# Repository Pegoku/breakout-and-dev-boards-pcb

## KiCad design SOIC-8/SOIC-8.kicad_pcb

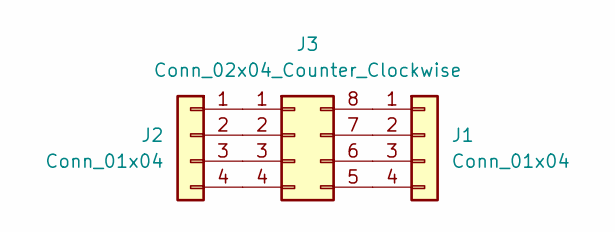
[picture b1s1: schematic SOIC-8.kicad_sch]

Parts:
J1, J2: Conn_01x04; PinHeader_1x04_P2.54mm_Vertical
J3: Conn_02x04_Counter_Clockwise; SOIC-8-1EP_3.9x4.9mm_P1.27mm_EP2.62x3.51mm

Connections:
unnamed: J1.1, J3.8
unnamed: J1.2, J3.7
unnamed: J1.3, J3.6
unnamed: J1.4, J3.5
unnamed: J2.1, J3.1
unnamed: J2.2, J3.2
unnamed: J2.3, J3.3
unnamed: J2.4, J3.4

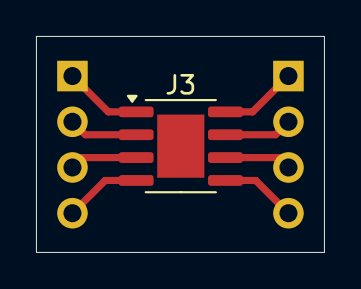
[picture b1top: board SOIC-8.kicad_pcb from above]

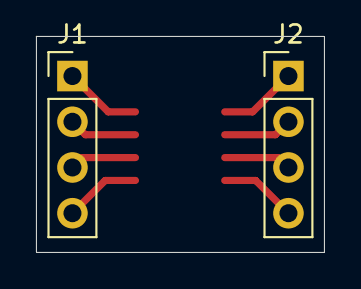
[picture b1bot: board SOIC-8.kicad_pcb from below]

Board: 2 copper layers, 16.0 x 12.0 mm, 3 parts (2 on the bottom side), 8 nets.

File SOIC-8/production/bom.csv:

Designator,Footprint,Quantity,Value,LCSC Part #
"J1, J2",PinHeader_1x04_P2.54mm_Vertical,2,Conn_01x04,
J3,SOIC-8-1EP_3.9x4.9mm_P1.27mm_EP2.62x3.51mm,1,Conn_02x04_Counter_Clockwise,

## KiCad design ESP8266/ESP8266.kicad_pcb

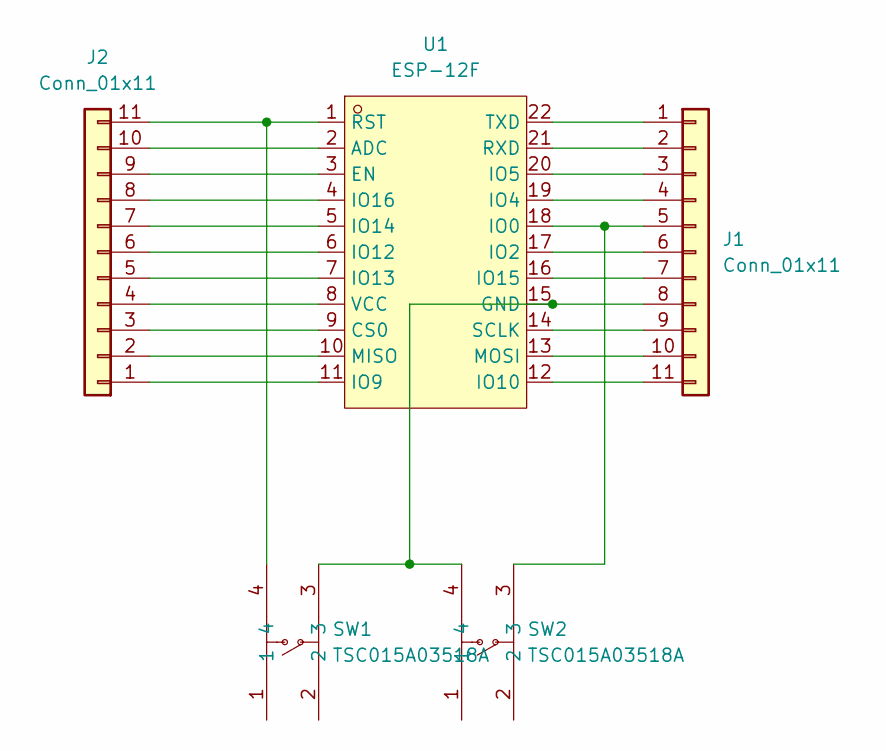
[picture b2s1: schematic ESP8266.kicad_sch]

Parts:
J1, J2: Conn_01x11; PinHeader_1x11_P2.54mm_Vertical
SW1, SW2: TSC015A03518A; KEY-SMD_4P-L4.5-W4.5-P3.00-LS6.8; LCSC Part C2888502
U1: ESP-12F; WIRELM-SMD_ESP-12F; LCSC Part C19949064

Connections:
unnamed: J1.1, U1.22 (TXD)
unnamed: J1.2, U1.21 (RXD)
unnamed: J1.3, U1.20 (IO5)
unnamed: J1.4, U1.19 (IO4)
unnamed: J1.5, SW2.3, U1.18 (IO0)
unnamed: J1.6, U1.17 (IO2)
unnamed: J1.7, U1.16 (IO15)
unnamed: J1.8, SW1.3, SW2.4, U1.15 (GND)
unnamed: J1.9, U1.14 (SCLK)
unnamed: J1.10, U1.13 (MOSI)
unnamed: J1.11, U1.12 (IO10)
unnamed: J2.1, U1.11 (IO9)
unnamed: J2.2, U1.10 (MISO)
unnamed: J2.3, U1.9 (CS0)
unnamed: J2.4, U1.8 (VCC)
unnamed: J2.5, U1.7 (IO13)
unnamed: J2.6, U1.6 (IO12)
unnamed: J2.7, U1.5 (IO14)
unnamed: J2.8, U1.4 (IO16)
unnamed: J2.9, U1.3 (EN)
unnamed: J2.10, U1.2 (ADC)
unnamed: J2.11, SW1.4, U1.1 (RST)

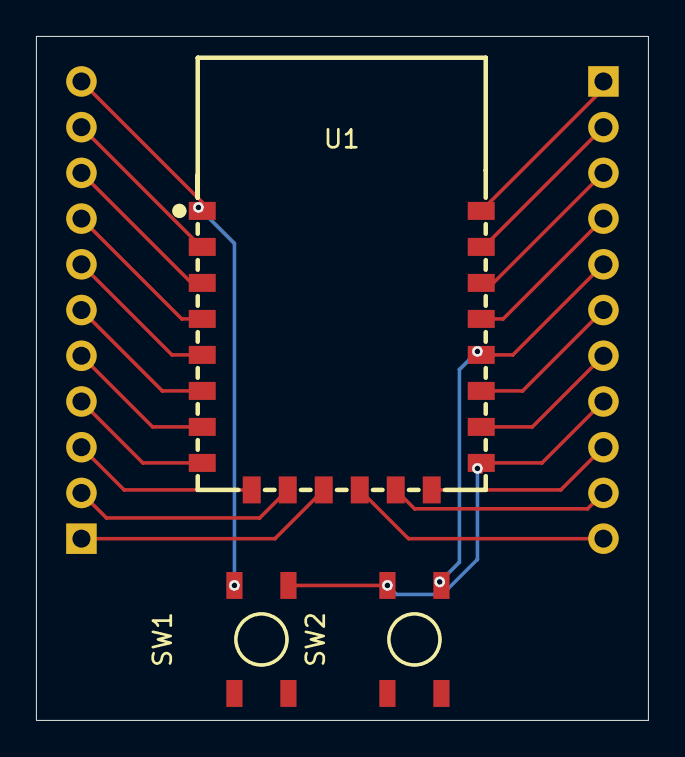
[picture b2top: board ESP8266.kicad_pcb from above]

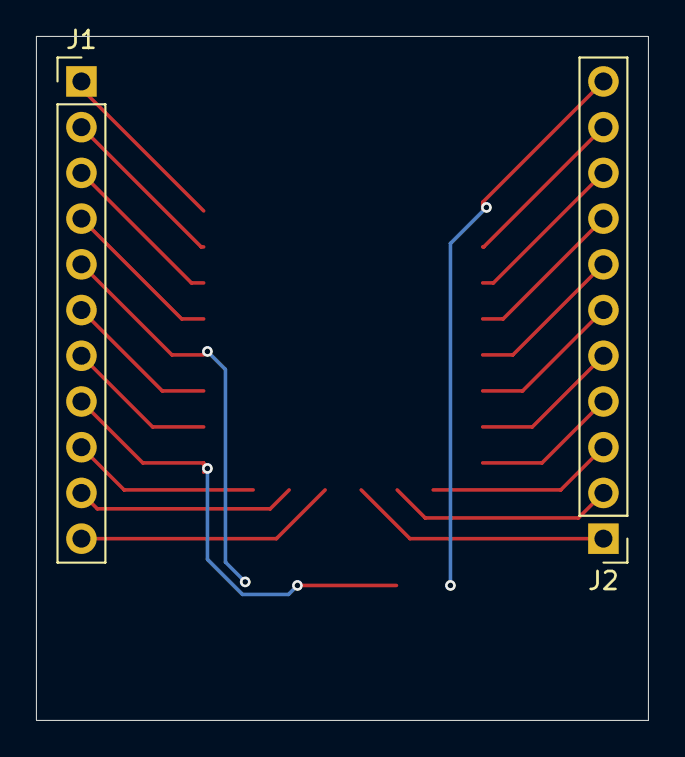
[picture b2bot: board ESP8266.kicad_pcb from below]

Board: 2 copper layers, 34.0 x 38.0 mm, 5 parts (2 on the bottom side), 22 nets.

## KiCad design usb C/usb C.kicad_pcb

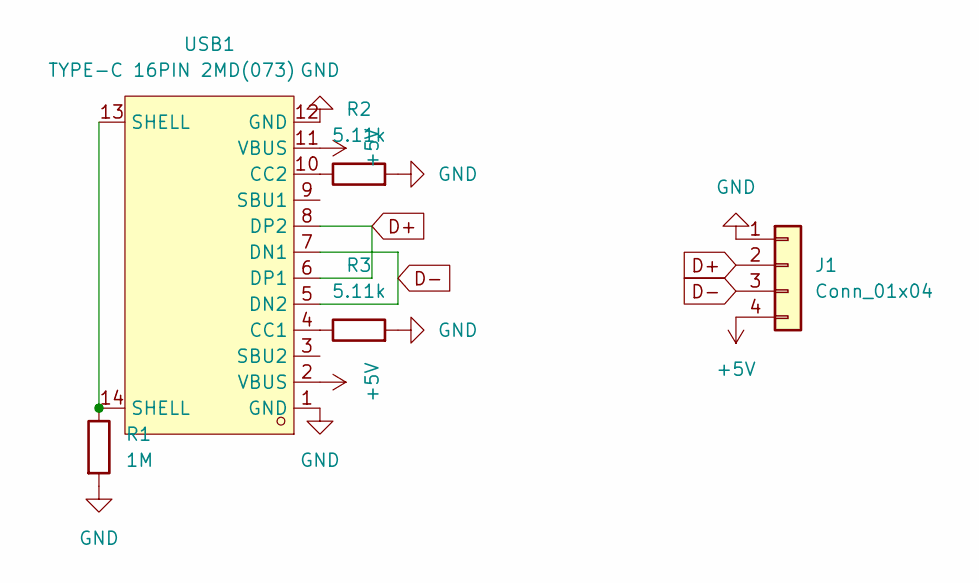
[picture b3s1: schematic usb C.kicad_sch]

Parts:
J1: Conn_01x04; PinHeader_1x04_P2.54mm_Horizontal
R1: 1M; R_0805_2012Metric
R2, R3: 5.11k; R_0805_2012Metric
USB1: TYPE-C 16PIN 2MD(073); USB-C-SMD_TYPE-C-6PIN-2MD-073; LCSC Part C2765186

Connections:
+5V: J1.4, USB1.2 (VBUS), USB1.11 (VBUS)
D+: J1.2, USB1.6 (DP1), USB1.8 (DP2)
D-: J1.3, USB1.5 (DN2), USB1.7 (DN1)
GND: J1.1, R1.2, R2.2, R3.2, USB1.1 (GND), USB1.12 (GND)
unnamed: R1.1, USB1.13 (SHELL), USB1.14 (SHELL)
unnamed: R3.1, USB1.4 (CC1)
unnamed: R2.1, USB1.10 (CC2)

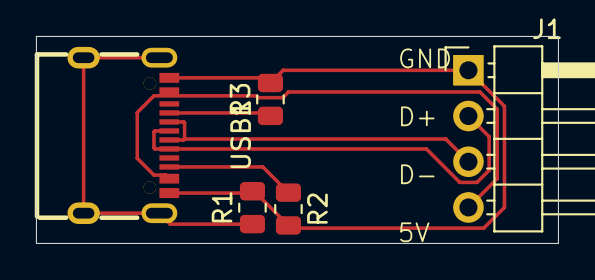
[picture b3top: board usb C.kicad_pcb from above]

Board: 2 copper layers, 29.0 x 11.5 mm, 5 parts (0 on the bottom side), 7 nets.

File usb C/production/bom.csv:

Designator,Footprint,Quantity,Value,LCSC Part #
J1,PinHeader_1x04_P2.54mm_Horizontal,1,Conn_01x04,
R1,0805,1,1M,
"R2, R3",0805,2,5.11k,
USB1,USB-C-SMD_TYPE-C-6PIN-2MD-073,1,TYPE-C 16PIN 2MD(073),C2765186

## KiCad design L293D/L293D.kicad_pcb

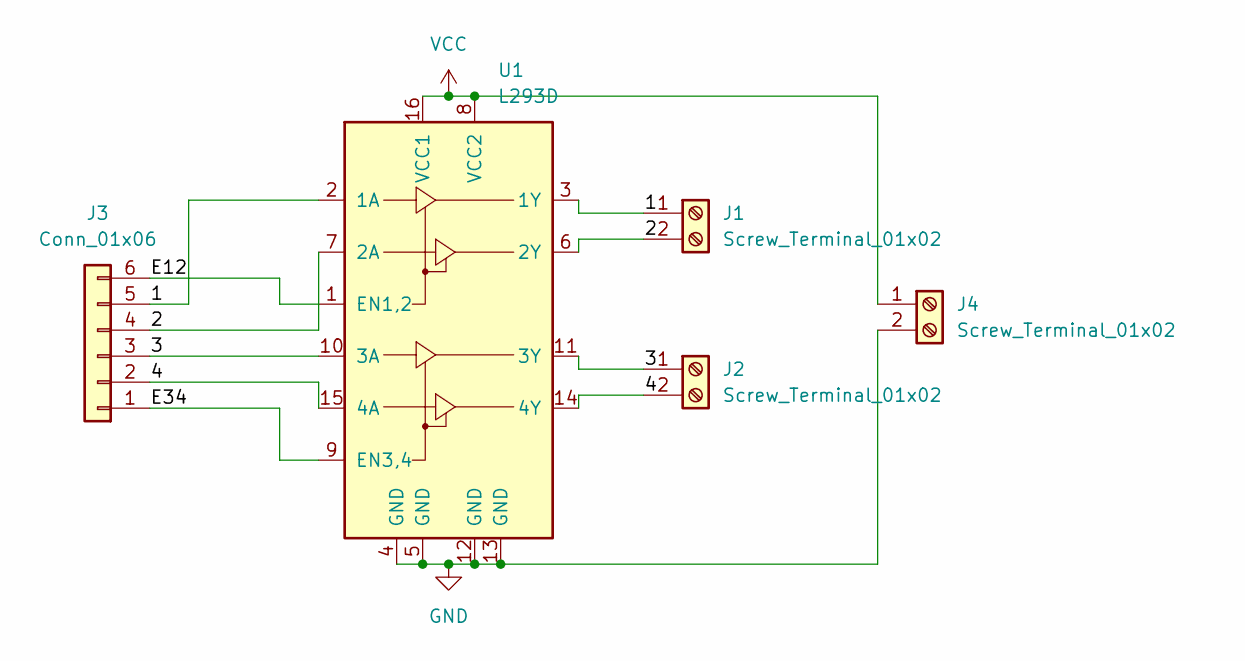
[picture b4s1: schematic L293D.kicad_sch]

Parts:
J1, J2, J4: Screw_Terminal_01x02; TerminalBlock_Phoenix_MKDS-1,5-2-5.08_1x02_P5.08mm_Horizont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
J3: Conn_01x06; PinSocket_1x06_P2.54mm_Vertical
U1: L293D; DIP-16_W7.62mm

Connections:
/1: J1.1, J3.5, U1.2 (1A), U1.3 (1Y)
/2: J1.2, J3.4, U1.6 (2Y), U1.7 (2A)
/3: J2.1, J3.3, U1.10 (3A), U1.11 (3Y)
/4: J2.2, J3.2, U1.14 (4Y), U1.15 (4A)
/E12: J3.6, U1.1 (EN1,2)
/E34: J3.1, U1.9 (EN3,4)
GND: J4.2, U1.4 (GND), U1.5 (GND), U1.12 (GND), U1.13 (GND)
VCC: J4.1, U1.8 (VCC2), U1.16 (VCC1)

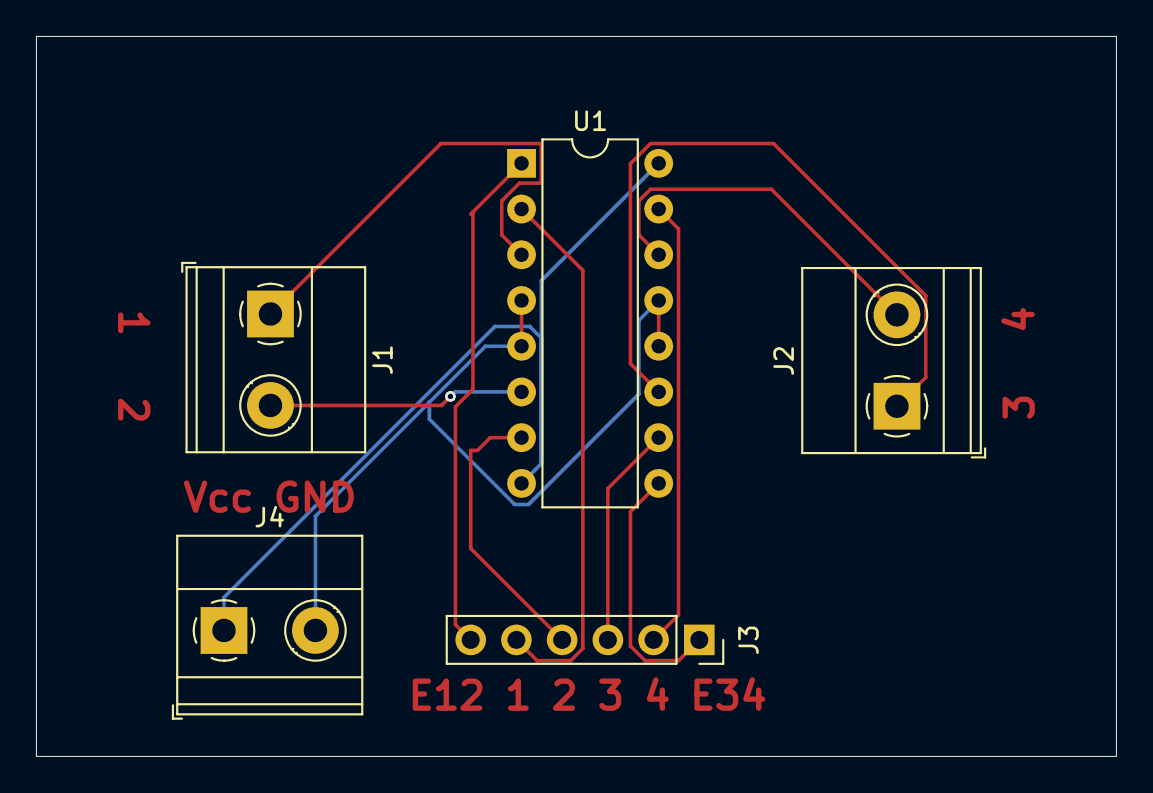
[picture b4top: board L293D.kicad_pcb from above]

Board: 2 copper layers, 60.0 x 40.0 mm, 5 parts (0 on the bottom side), 8 nets.

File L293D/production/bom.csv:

Designator,Footprint,Quantity,Value,LCSC Part #
"J1, J2, J4","TerminalBlock_Phoenix_MKDS-1,5-2-5.08_1x02_P5.08mm_Horizontal",3,Screw_Terminal_01x02,
J3,PinSocket_1x06_P2.54mm_Vertical,1,Conn_01x06,
U1,DIP-16_W7.62mm,1,L293D,

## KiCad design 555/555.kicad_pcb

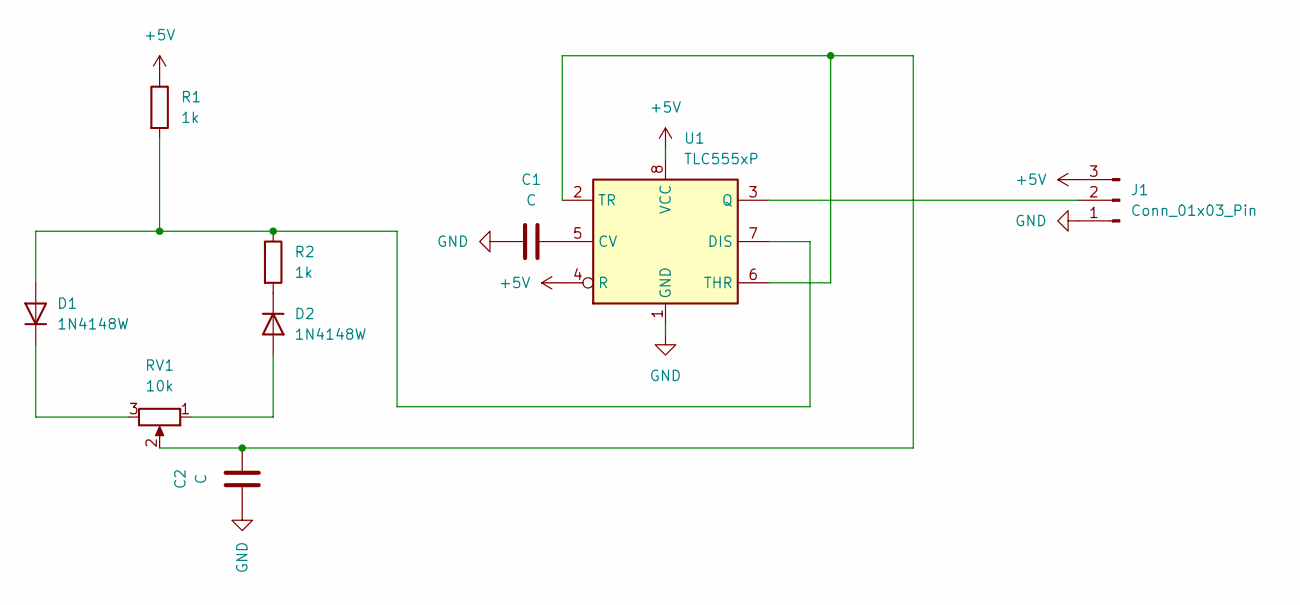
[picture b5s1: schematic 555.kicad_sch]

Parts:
C1, C2: C; C_1206_3216Metric
D1, D2: 1N4148W; D_SOD-123
J1: Conn_01x03_Pin; PinHeader_1x03_P2.54mm_Vertical
R1, R2: 1k; R_0805_2012Metric
RV1: 10k; RES-ADJ-TH_3362P; LCSC C118956
U1: TLC555xP; SOIC-8_3.9x4.9mm_P1.27mm

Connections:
+5V: J1.3, R1.1, U1.4 (R), U1.8 (VCC)
GND: C1.1, C2.1, J1.1, U1.1 (GND)
unnamed: D1.2 (A), R1.2, R2.1, U1.7 (DIS)
unnamed: D1.1 (K), RV1.3
unnamed: D2.2 (A), RV1.1
unnamed: D2.1 (K), R2.2
unnamed: J1.2, U1.3 (Q)
unnamed: C1.2, U1.5 (CV)
unnamed: C2.2, RV1.2, U1.2 (TR), U1.6 (THR)

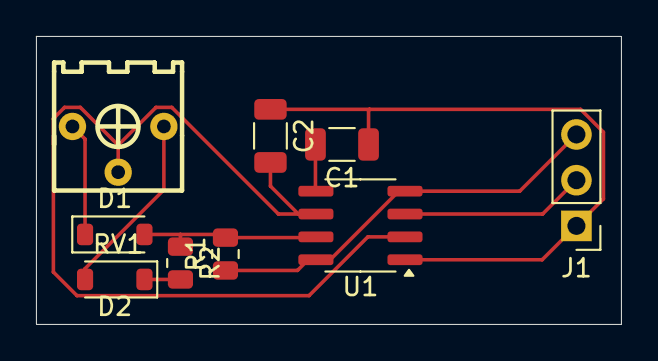
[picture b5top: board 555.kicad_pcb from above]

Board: 2 copper layers, 32.5 x 16.0 mm, 9 parts (0 on the bottom side), 9 nets.

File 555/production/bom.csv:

Designator,Footprint,Quantity,Value,LCSC Part #
"C1, C2",1206,2,C,
"D1, D2",D_SOD-123,2,1N4148W,
J1,PinHeader_1x03_P2.54mm_Vertical,1,Conn_01x03_Pin,
"R1, R2",0805,2,1k,
RV1,RES-ADJ-TH_3362P,1,10k,C118956
U1,SOIC-8_3.9x4.9mm_P1.27mm,1,TLC555xP,

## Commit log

2024-08-10 start
2024-08-10 schematic
2024-08-10 schematic done
2024-08-10 pcb time
2024-08-10 done
2024-08-10 finished 555
2024-08-10 L293D
2024-08-10 scheematic
2024-08-10 finish
2024-08-11 relay
2024-08-11 commit PCB
2024-08-11 USB A
2024-08-11 usb c
2024-08-11 ESP8266
2024-08-11 soic-8
2024-08-15 completed
2024-08-15 completed 2
